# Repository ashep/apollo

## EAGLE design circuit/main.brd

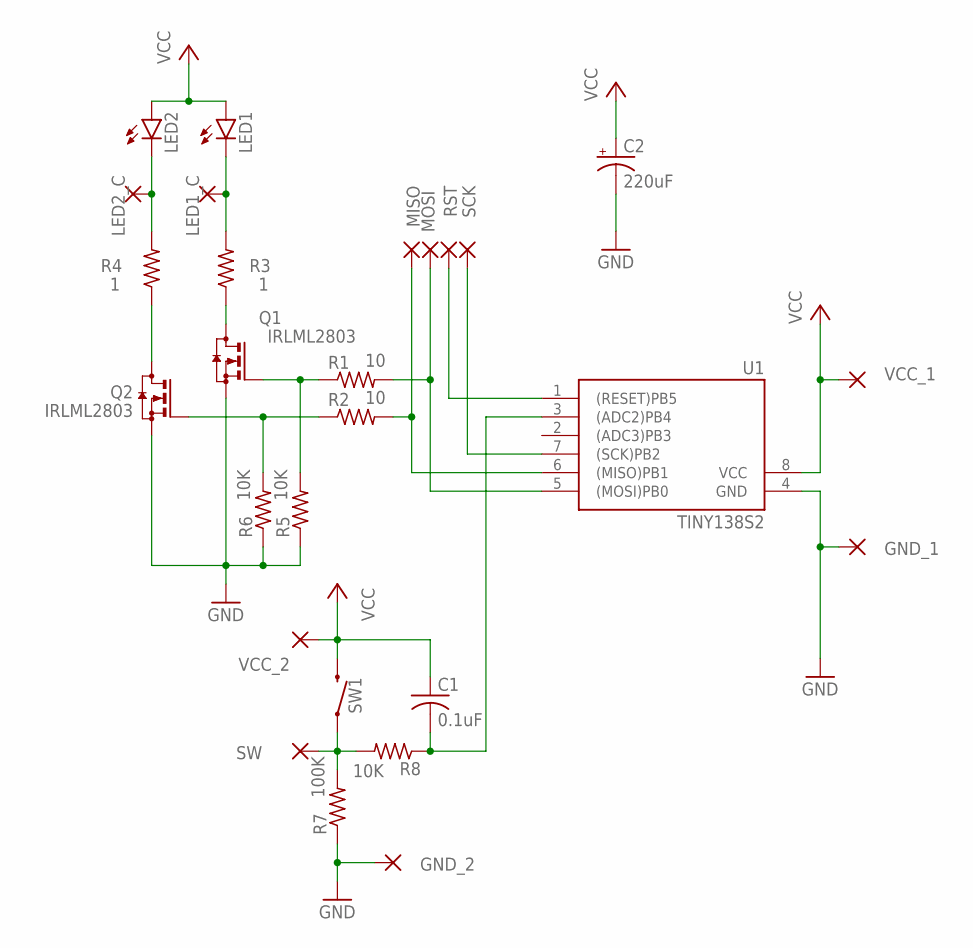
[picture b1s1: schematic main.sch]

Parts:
C1: 0.1uF; C0805
C2: 220uF; E2,5-6E
GND_1, GND_2: 1,6/0,9
LED1, LED2: Z-POWER-LED; Z-POWER-LED-PCB-TYPE
LED1_C, LED2_C: 1,6/0,9
MISO: 1,6/0,9
MOSI: 1,6/0,9
Q1, Q2: IRLML2803; SOT23
R1, R2: 10; R0805
R3, R4: 1; 0309/10
R5, R6, R8: 10K; R0805
R7: 100K; R0805
RST: 1,6/0,9
SCK: 1,6/0,9
SW: 1,6/0,9
SW1: MOMENTARY-SWITCH-SPST-PTH-6.0MM; TACTILE_SWITCH_PTH_6.0MM
U1: TINY138S2; SO08
VCC_1, VCC_2: 1,6/0,9

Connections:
GND: C2.-, GND_1.1, GND_2.1, Q1.2 (S), Q2.2 (S), R5.1, R6.1, R7.1, U1.4 (GND)
LED1_C: LED1.C, LED1_C.1, R3.2
LED2_C: LED2.C, LED2_C.1, R4.2
MISO: MISO.1, R2.2, U1.6 ((MISO)PB1)
MOSI: MOSI.1, R1.2, U1.5 ((MOSI)PB0)
PB4: C1.2, R8.1, U1.3 ((ADC2)PB4)
Q1_D: Q1.3 (D), R3.1
Q1_G: Q1.1 (G), R1.1, R5.2
Q2_D: Q2.3 (D), R4.1
Q2_G: Q2.1 (G), R2.1, R6.2
RESET: RST.1, U1.1 ((RESET)PB5)
SCK: SCK.1, U1.7 ((SCK)PB2)
SW1: R7.2, R8.2, SW.1, SW1.1
VCC: C1.1, C2.+, LED1.A, LED2.A, SW1.3 (2), U1.8 (VCC), VCC_1.1, VCC_2.1

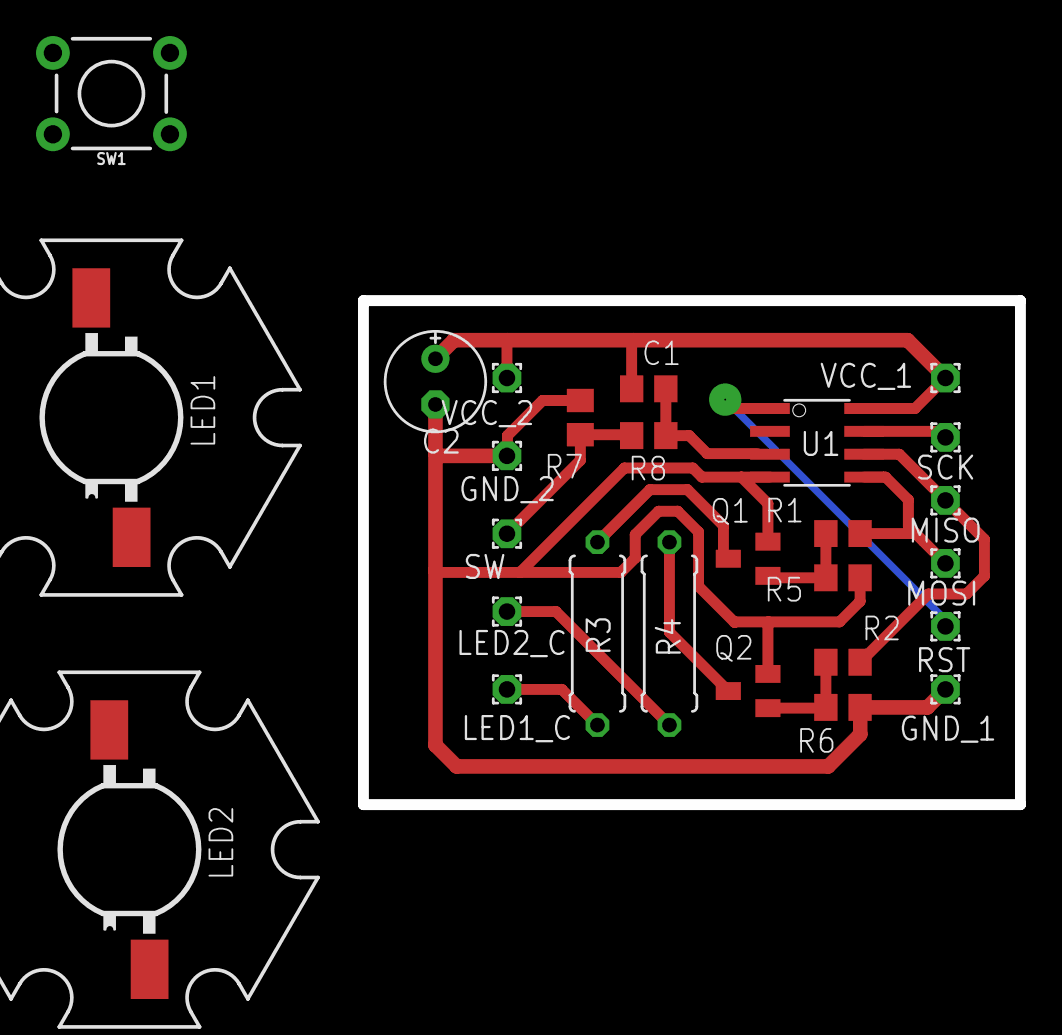
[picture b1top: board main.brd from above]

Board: 2 copper layers, 36.5 x 28.0 mm, 27 parts (0 on the bottom side), 14 nets.

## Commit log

2019-10-06 STL models added
2019-10-06 Circuit added

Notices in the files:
parts and their libraries:
SparkFun-Switches: Licensing: Creative Commons ShareAlike 4.0 International - https://creativecommons.org/licenses/by-sa/4.0
